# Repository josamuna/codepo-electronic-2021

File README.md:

# Monitor Engine - ULB / CODEPO

> Cette partie est le complément logique du module logiciel fait par les étudiants de l'[ISIG-Goma](https://www.isig.ac.cd/) qui se trouve successivement dans ces deux répository ([Backend](https://github.com/josamuna/codepo-backend) et [Frontend](https://github.com/josamuna/codepo-fontend)).

## Table des Matières

1. [Introduction](#Introduction)
2. [Liste des composants électroniques](#Composants)
3. [Schémas électroniques et PCB](#Schémas)
4. [Outils de developpement du code source](#Outils-developpement)
5. [Structure du projet](#Structure)
6. [Utilisation des commandes AT et Thingstream](#Commandes-AT-Thingstream)
7. [Fonctionnement du module électronique](#Fonctionnement)
8. [Récommandations](#Récommandations)
9. [Sponsors](#Sponsors)
10. [Contributeurs](#Contributeurs)
11. [Licence](#Licence)

### Introduction

***

### Liste des composants électroniques

***

### Schémas électroniques et PCB

Le [schéma global](hardware/MSF-Battery-monitor.pdf) est disponible dans le dossier [*hardware*](hardware).

Il peut être divisé en

### Outils de developpement du code source

***

### Structure du projet

***

La structure du projet reprend les dossiers et fichiers suivants détaillés dans cette arborescence:

```
.\
│
├── build\
│   └── default\
│       └── production\
│           ├── adc.o
│           ├── adc.o.d
│           ├── init.o
│           ├── init.o.d
│           ├── main.o
│           ├── main.o.d
│           ├── thingstream.o
│           ├── thingstream.o.d
│           ├── uart1.o
│           └── uart1.o.d
│
├── debug\
│   └── default\
│
│
├── dist\
│   └── default\
│       └── production\
│           ├── codepo-electronic-2021.production.elf
│           ├── codepo-electronic-2021.production.hex
│           ├── codepo-electronic-2021.production.map
│           └── memoryfile.xml
│
├── nbproject\
│   ├── private\
│   │   ├── configurations.xml
│   │   ├── private.xml
│   │   └── SuppressibleMessageMemo.properties
│   │
│   ├── configurations.xml
│   ├── Makefile-default.mk
│   ├── Makefile-genesis.properties
│   ├── Makefile-impl.mk
│   ├── Makefile-local-default.mk
│   ├── Makefile-variables.mk
│   ├── Package-default.bash
│   └── project.xml
│
├── adc.c
├── adc.h
├── init.c
├── init.h
├── LICENSE
├── main.c
├── main.c.dump
├── Makefile
├── README.md
├── thingstream.c
├── thingstream.h
├── uart1.c
├── uart1.h
├── uart1.h.dump
├── uart2.c
└── uart2.h
```

- `..\build\` est le répertoire principal de génération des fichiers objects après compilation. 
- `..\dist\` répertorie de génération des fichier d'utilisation en production.
- `..\nbproject\` répertoire de configuration de l'IDE.
- `..\adc.c` est le fichier permettant d'initialiser la conversion anologue vers digital
- `..\adc.h` est le header du fichier adc.c
- `..\init.c` est le fichier permettant d'initialiser les paramètres du microcontroleur
- `..\init.h` est le header du fichier init.c
- `..\LICENSE` ...............
- `..\main.c` est le fichier principal d'entré du programme. C'est ici que commence l'éxécution du code par le compilateur.
- `..\main.c.dump` ...............
- `..\Makefile` ...............
- `..\README.md` le fichier contenant la documentation du projet.
- `..\thingstream.c` est le fichier contenant les différentes fonctions qui permettent d'envoyer des commandes au module de communication Thingstream Click via l'UART afin de, par exemple, se connecter au reseau, recevoir des messages, en envoyer, etc.
- `..\thingstream.h` est le header du fichier thingstream.c
- `..\uart1.c` est le fichier qui permet la communication UART via 2 pattes (TX et RX) du micro-controleur (communication entre le micro-controleur et le module de communication Thingstream Click)
- `..\uart1.h` est le header du ficier uart1.c
- `..\uart1.dump` ...............
- `..\uart2.c`  est le fichier qui permet la communication UART via 2 autres pattes (TX et RX) du micro-controleur
- `..\uart2.h` est le header du fichier uart2.c
- `..\adc.c` ...............

### Utilisation des commandes AT et Thingstream

***

### Fonctionnement du module électronique

***

### Récommandations

***

### Sponsors

1. En tant que sponsors prépondérant, l'[ULB (Université Libre de Bruxelles)-CODEPO (Cellule de Coopération au Développement de l'Ecole Polytechnique de Bruxelles)](https://polytech.ulb.be/fr/international/cellule-de-cooperation-au-developpement) au sein de la CODEPO assure la mise au point de ce module électronique.

2. Comme financier, l'[ARES(Académie de Recherche et d'Enseignement Supérieur)](https://www.ares-ac.be/fr/) finance bon nombre des activités du projet. ***Il est le bailleur de fond numéro 1***. Néanmoins, l'***ULB*** en tant qu'Institution d'implémentation de la solution, en assure les financements subsidiaires et fournit sa main d'oeuvre (Encadrants, Experts et étudiants).

3. Pour sa par prépondérante dans la collaboration, l'[ISIG (Institut Supérieur d'Informatique et de Gestion de Goma)](https://www.isig.ac.cd/) assure la mise en place de la plateforme logiciel devant communiquer avec le module électronique.

### Contributeurs

***

 Plusieurs personnes ont apporté leurs pierres dans la mise au point de ce logiciel pour la part de l'ULB et de lISIG, nous rémercions: 
- **Alban Dietrich**: <alban.dietrich@ulb.ac.be>.
- **Antoine Nonclercq** : `+3226503086` , <anoncler@ulb.ac.cd>.
- **Arnaud Depuydt**: <Arnaud.Depuydt@ulb.be>.
- **Cecile Castiaux**. <Cecile.Castiaux@ulb.be>.
- **Josué Isamuna** : `+243972727527` , <josueisamuna@isig.ac.cd>, <https://github.com/josamuna>.
- **Margaux Mannaerts** : <Margaux.Mannaerts@ulb.be>.
- **Maxime Petre** : <vitaltakanic@gmail.com>.
- **Michel Osée** : `+243994814807` , <Michel.Osee@ulb.be>, <https://github.com/miosee>.
- **Nathan Gartner** : <Nathan.Gartner@ulb.be>.
- **Nicolas Wallemacq** : `+32474769804` , <Nicolas.Wallermacq@ulb.be>, <https://github.com/NicolasWa>.
- **Orianne Bastin** : `+3226502838` , <orianne.bastin@ulb.be>.
- **Philippe Mutijima** : <Philippe.Mwansa.Mutijima@ulb.be>.
- **Philippe Questel** : `+32474769804` , <Philippe.Questel@ulb.be>.

### License

***

Ce projet est par ailleurs soumis au droits relatifs à la licence [MIT](https://mit-license.org/).

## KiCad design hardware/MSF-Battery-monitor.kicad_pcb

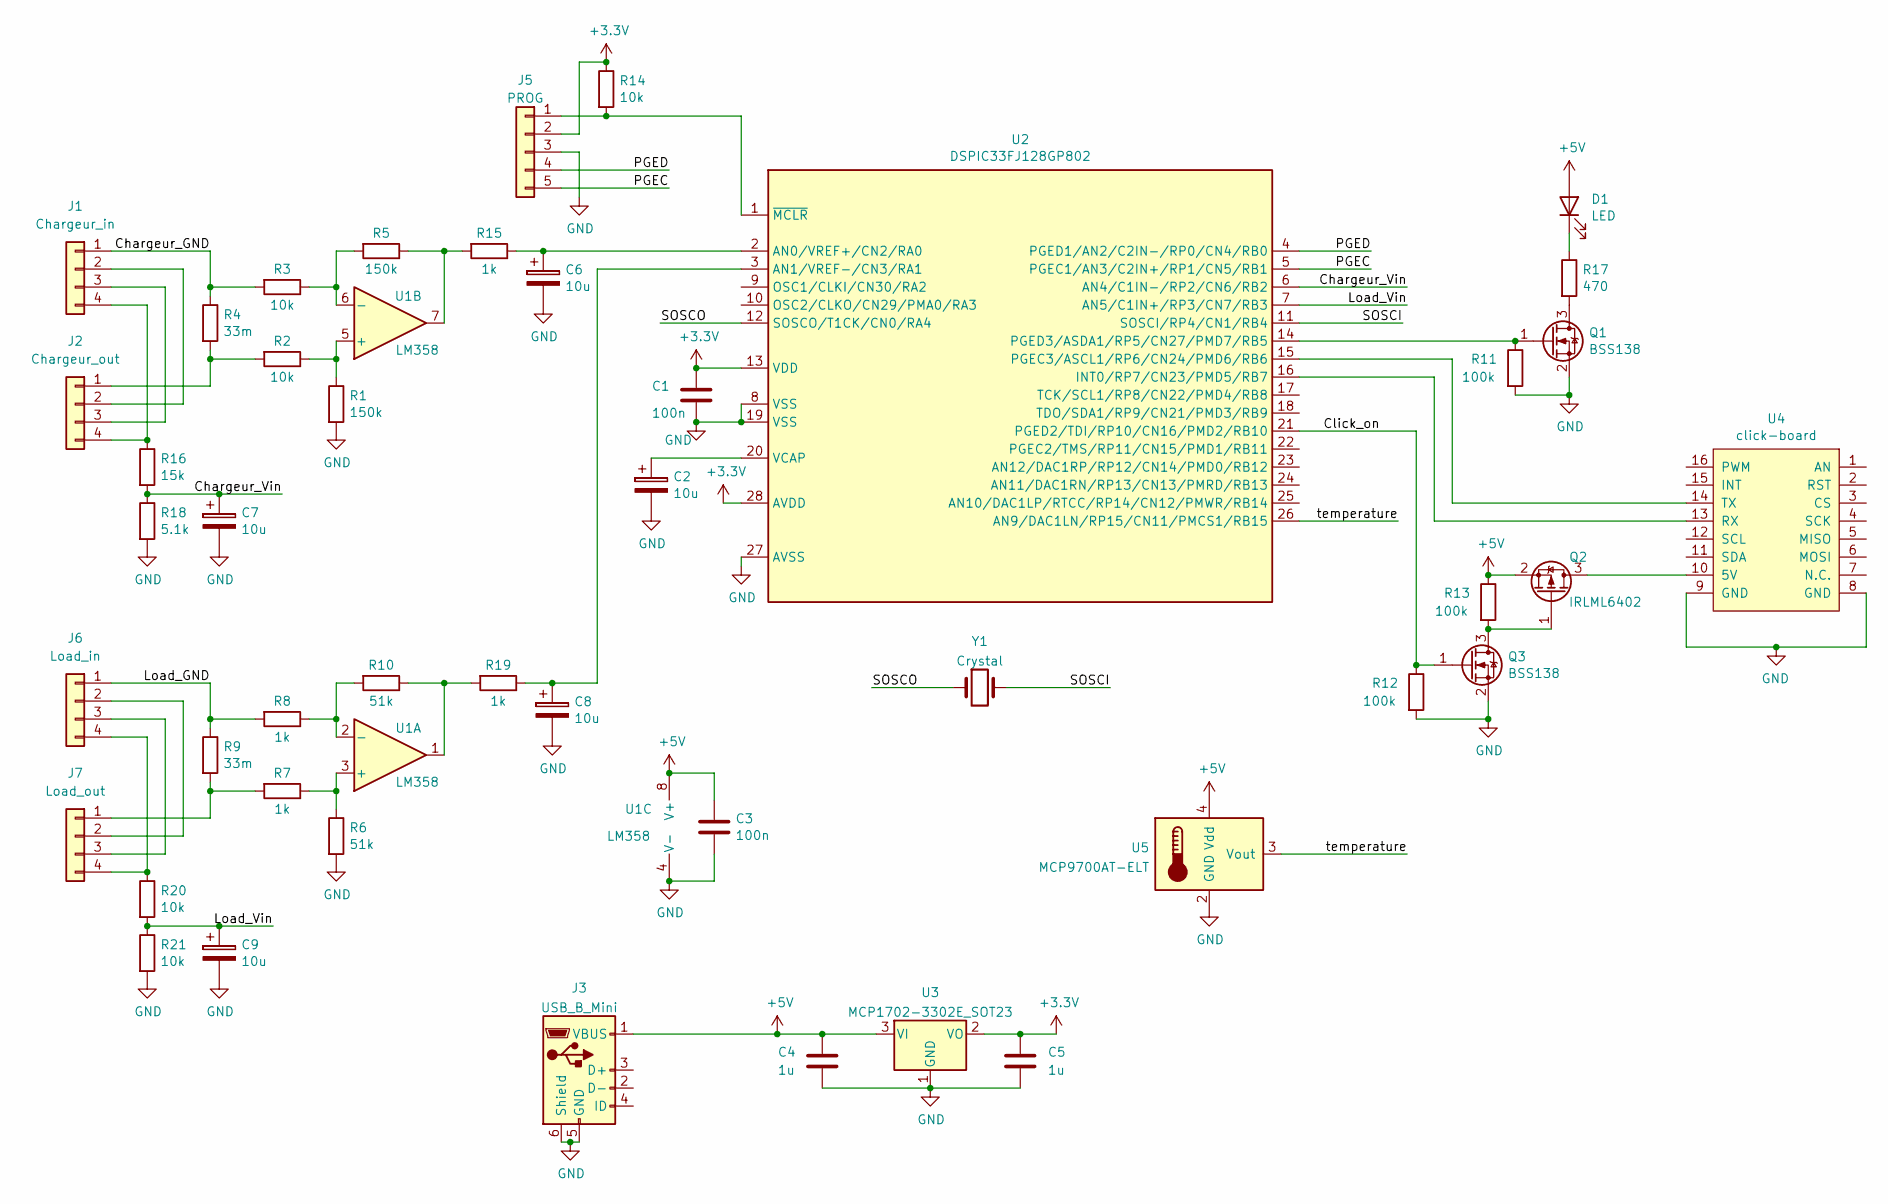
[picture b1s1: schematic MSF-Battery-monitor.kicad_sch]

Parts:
C1, C3: 100n; C_Disc_D7.0mm_W2.5mm_P5.00mm
C2, C6, C7, C8, C9: 10u; CP_Radial_D6.3mm_P2.50mm
C4, C5: 1u; C_0805_2012Metric_Pad1.18x1.45mm_HandSolder
D1: LED; LED_1206_3216Metric_Pad1.42x1.75mm_HandSolder
J1: Chargeur_in; PinHeader_1x04_P2.54mm_Vertical
J2: Chargeur_out; PinHeader_1x04_P2.54mm_Vertical
J3: USB_B_Mini; USB_Micro-B_Molex-105017-0001
J5: PROG; PinHeader_1x05_P2.54mm_Vertical
J6: Load_in; PinHeader_1x04_P2.54mm_Vertical
J7: Load_out; PinHeader_1x04_P2.54mm_Vertical
Q1, Q3: BSS138; SOT-23
Q2: IRLML6402; SOT-23
R1, R5: 150k; R_Axial_DIN0207_L6.3mm_D2.5mm_P10.16mm_Horizontal
R2, R3, R14, R20, R21: 10k; R_Axial_DIN0207_L6.3mm_D2.5mm_P10.16mm_Horizontal
R4, R9: 33m; R_2512_6332Metric_Pad1.52x3.35mm_HandSolder
R6, R10: 51k; R_Axial_DIN0207_L6.3mm_D2.5mm_P10.16mm_Horizontal
R7, R8, R15, R19: 1k; R_Axial_DIN0207_L6.3mm_D2.5mm_P10.16mm_Horizontal
R11, R12, R13: 100k; R_0805_2012Metric_Pad1.15x1.40mm_HandSolder
R16: 15k; R_Axial_DIN0207_L6.3mm_D2.5mm_P10.16mm_Horizontal
R17: 470; R_0805_2012Metric_Pad1.15x1.40mm_HandSolder
R18: 5.1k; R_Axial_DIN0207_L6.3mm_D2.5mm_P10.16mm_Horizontal
U1: LM358; DIP-8_W7.62mm_LongPads
U2: DSPIC33FJ128GP802; DIP-28_W7.62mm_LongPads
U3: MCP1702-3302E_SOT23; SOT-23
U4: click-board; Click-board
U5: MCP9700AT-ELT; SOT-353_SC-70-5
Y1: Crystal; Crystal_AT310_D3.0mm_L10.0mm_Vertical

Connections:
+3V3: C1.1, C5.1, J5.2, R14.1, U2.13 (VDD), U2.28 (AVDD), U3.2 (VO)
+5V: C3.1, C4.1, D1.2 (A), J3.1 (VBUS), Q2.2 (S), R13.1, U1.8 (V+), U3.3 (VI), U5.4 (Vdd)
/Chargeur_GND: J1.1, R3.2, R4.1
/Chargeur_Vin: C7.1, R16.2, R18.1, U2.6 (AN4/C1IN-/RP2/CN6/RB2)
/Click_on: Q3.1 (G), R12.1, U2.21 (PGED2/TDI/RP10/CN16/PMD2/RB10)
/Load_GND: J6.1, R8.2, R9.1
/Load_Vin: C9.1, R20.2, R21.1, U2.7 (AN5/C1IN+/RP3/CN7/RB3)
/PGEC: J5.5, U2.5 (PGEC1/AN3/C2IN+/RP1/CN5/RB1)
/PGED: J5.4, U2.4 (PGED1/AN2/C2IN-/RP0/CN4/RB0)
/SOSCI: U2.11 (SOSCI/RP4/CN1/RB4), Y1.2
/SOSCO: U2.12 (SOSCO/T1CK/CN0/RA4), Y1.1
/temperature: U2.26 (AN9/DAC1LN/RP15/CN11/PMCS1/RB15), U5.3 (Vout)
GND: C1.2, C2.2, C3.2, C4.2, C5.2, C6.2, C7.2, C8.2, C9.2, J3.5 (GND), J3.6 (Shield), J5.3, Q1.2 (S), Q3.2 (S), R1.2, R6.2, R11.2, R12.2, R18.2, R21.2, U1.4 (V-), U2.8 (VSS), U2.19 (VSS), U2.27 (AVSS), U3.1 (GND), U4.8 (GND), U4.9 (GND), U5.2 (GND)
unnamed: C2.1, U2.20 (VCAP)
unnamed: C6.1, R15.1, U2.2 (AN0/VREF+/CN2/RA0)
unnamed: C8.1, R19.1, U2.3 (AN1/VREF-/CN3/RA1)
unnamed: D1.1 (K), R17.1
unnamed: J1.2, J2.2
unnamed: J1.3, J2.3
unnamed: J1.4, J2.4, R16.1
unnamed: J2.1, R2.2, R4.2
unnamed: J5.1, R14.2, U2.1 (~MCLR)
unnamed: J6.2, J7.2
unnamed: J6.3, J7.3
unnamed: J6.4, J7.4, R20.1
unnamed: J7.1, R7.2, R9.2
unnamed: Q1.1 (G), R11.1, U2.14 (PGED3/ASDA1/RP5/CN27/PMD7/RB5)
unnamed: Q1.3 (D), R17.2
unnamed: Q2.1 (G), Q3.3 (D), R13.2
unnamed: Q2.3 (D), U4.10 (5V)
unnamed: R1.1, R2.1, U1.5 (+)
unnamed: R3.1, R5.2, U1.6 (-)
unnamed: R6.1, R7.1, U1.3 (+)
unnamed: R10.1, R19.2, U1.1
unnamed: R8.1, R10.2, U1.2 (-)
unnamed: R5.1, R15.2, U1.7
unnamed: U2.15 (PGEC3/ASCL1/RP6/CN24/PMD6/RB6), U4.14 (TX)
unnamed: U2.16 (INT0/RP7/CN23/PMD5/RB7), U4.13 (RX)

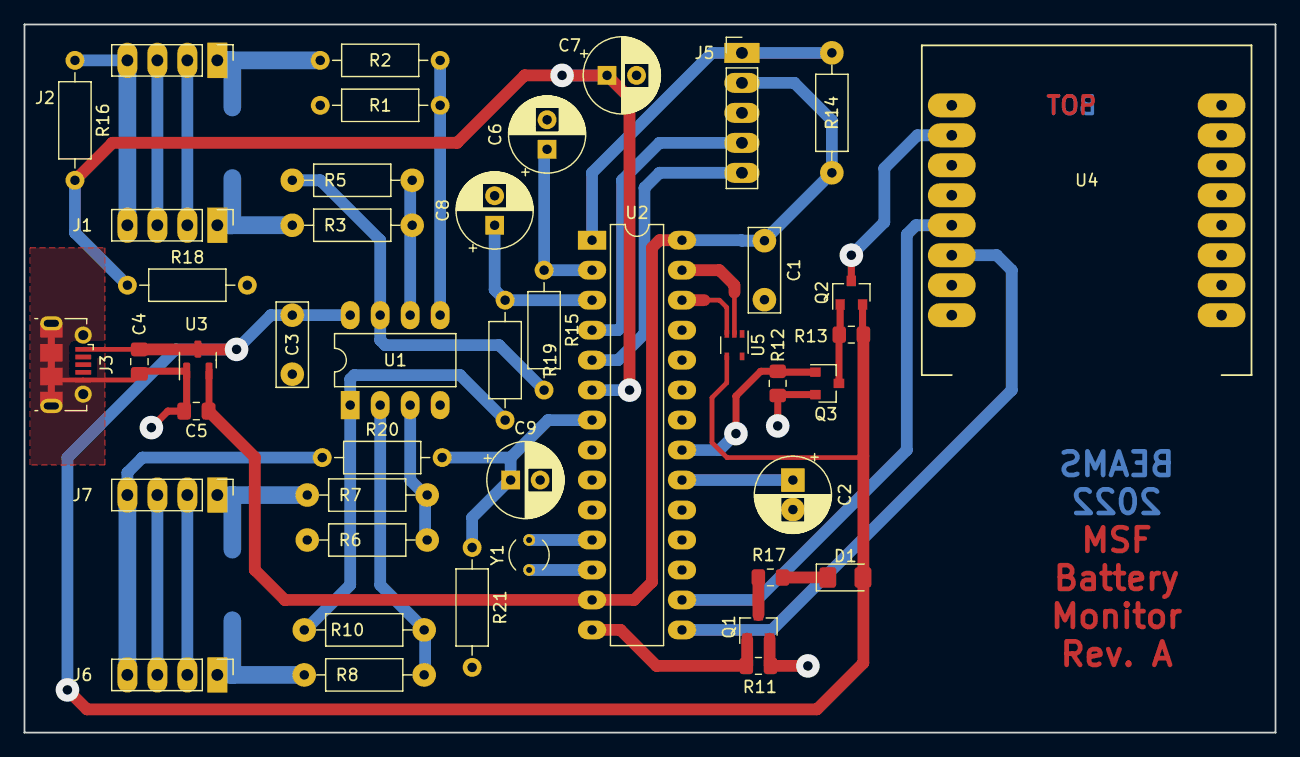
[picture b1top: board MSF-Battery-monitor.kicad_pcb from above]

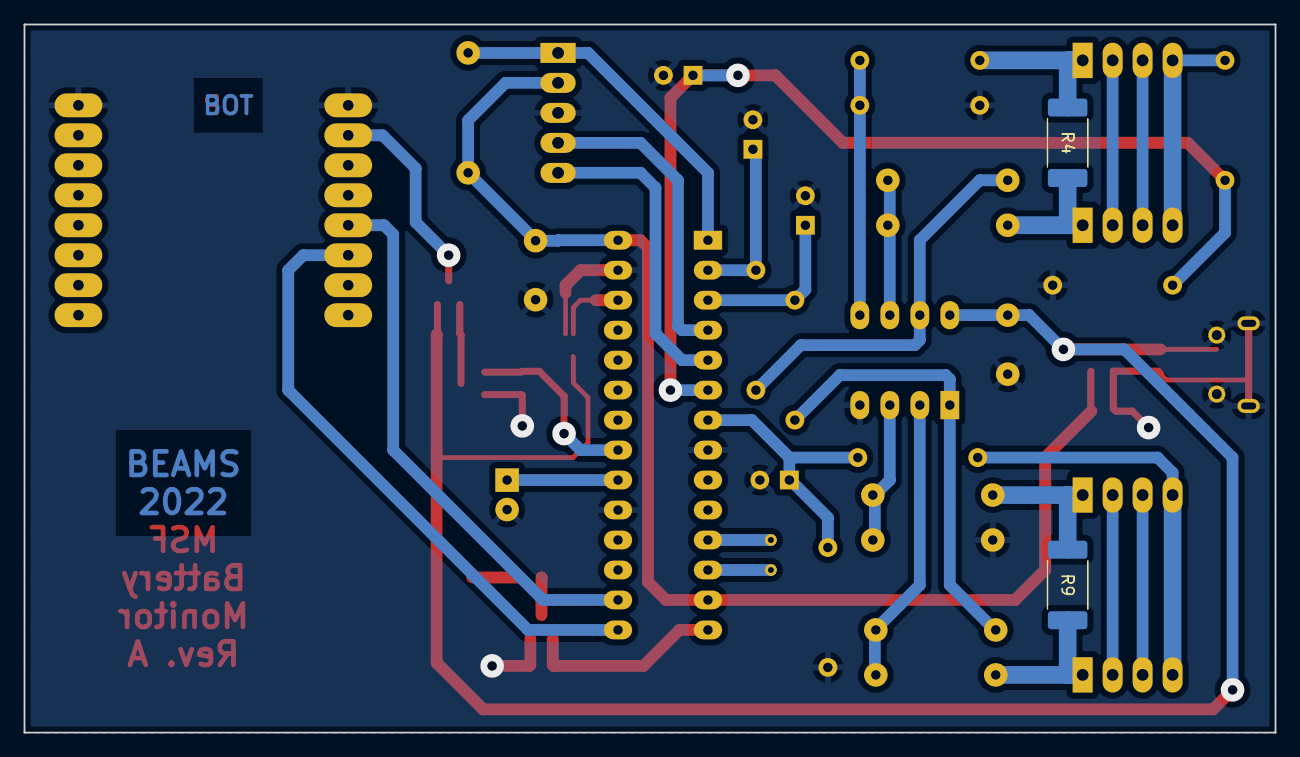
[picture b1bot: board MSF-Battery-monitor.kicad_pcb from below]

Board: 2 copper layers, 106.0 x 60.0 mm, 46 parts (2 on the bottom side), 38 nets.

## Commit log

2022-02-04 UpdateReadme.md-2022-02-04
2022-02-07 Update README.md
    adc.c est mentionné deux fois , est-ce normal? J'ai complété les pointillés des fonctions que nous avions faites. Les fichiers .dumps ne sont pas importants
2022-03-04 Réorganisation de l'arborescence + début de documentation
2022-03-14 Version test 10/03/2022
2022-03-14 Bug fix: lecture des messages du click
    En cas de message d'erreur, s'il est plus long que le message de succès, on ne lisait pas tous les caractères du message, ce qui se répercutait sur le message suivant.
2022-04-01 adaptation au nouveau PCB
    ajout d'une simulation de multi-modules
2022-04-25 seconde tentative
2022-04-28 Sleep sur batterie
2022-05-03 version avec timer1 isr
2022-05-03 passage au timer1 et mise à jour du PCB
